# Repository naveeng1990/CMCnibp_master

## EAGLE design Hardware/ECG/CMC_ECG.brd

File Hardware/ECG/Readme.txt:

Contains ecg pre-amplifier board design

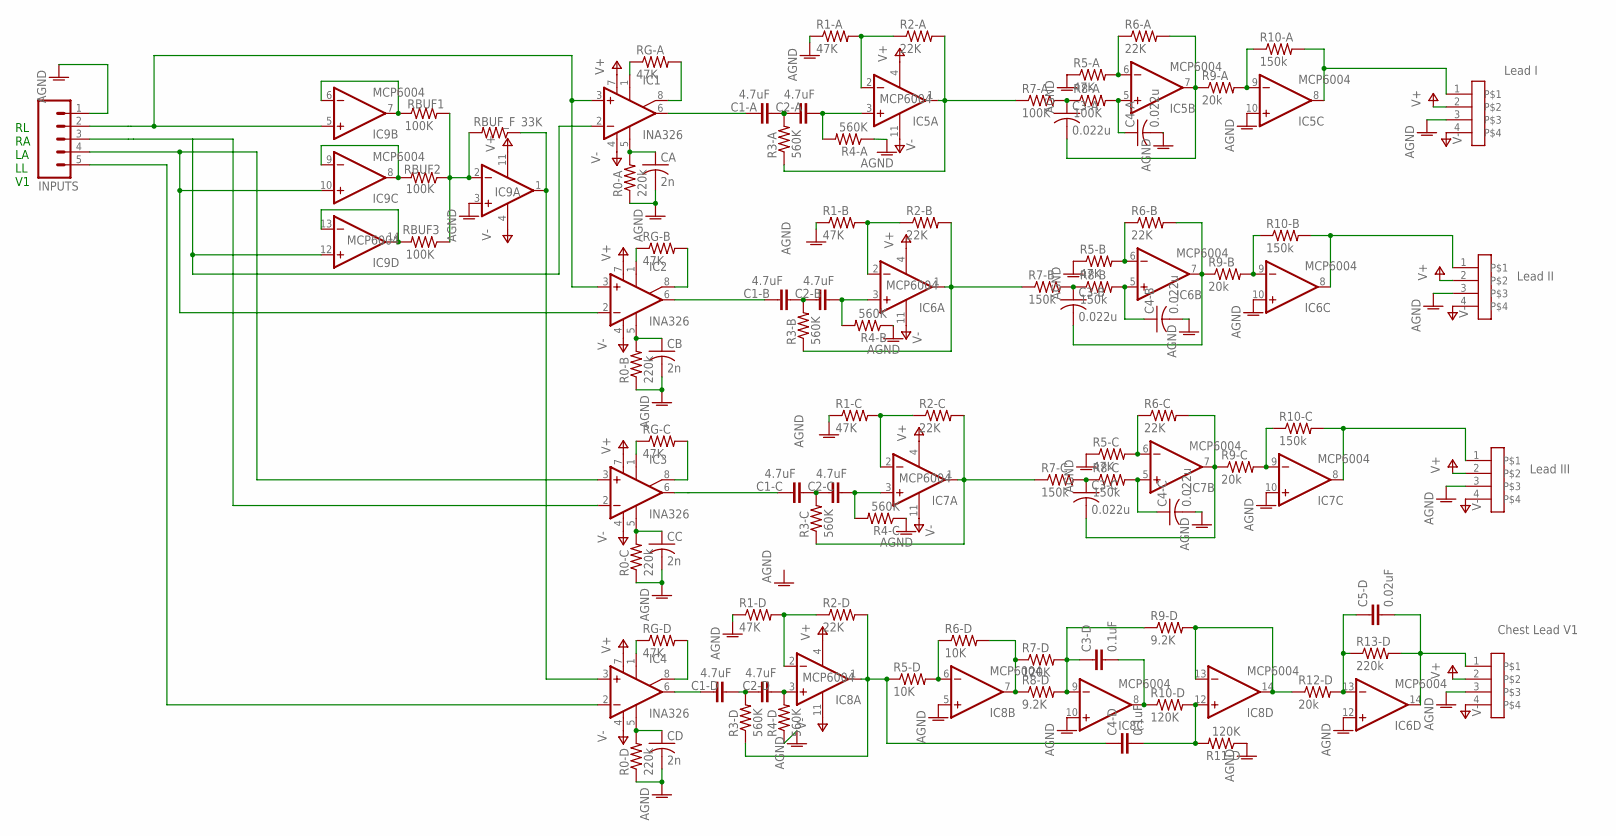
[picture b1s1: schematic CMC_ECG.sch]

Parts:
C1-A, C1-B, C1-C, C1-D, C2-A, C2-B, C2-C, C2-D: 4.7uF; C0805
C3-A, C3-B, C3-C, C4-A, C4-B, C4-C: 0.022u; C0805
C3-D, C4-D: 0.1uF; C0805
C5-D: 0.02uF; C0805
CA: 2n; C0805
CB: 2n; C0805
CC: 2n; C0805
CD: 2n; C0805
CHEST-V3: CON-4PIN_SIL; CON-4PIN-SIL
IC1, IC2, IC3, IC4: INA326; MSOP-08
IC5, IC6, IC7, IC8, IC9: MCP6004; TSSOP14
INPUTS: M05; 05P
LEAD-I: CON-4PIN_SIL; CON-4PIN-SIL
LEAD-II, LEAD-II1: CON-4PIN_SIL; CON-4PIN-SIL
R0-A, R0-B, R0-C, R0-D, R13-D: 220k; R0805
R1-A, R1-B, R1-C, R1-D, R5-A, R5-B, R5-C: 47K; R0805
R2-A, R2-B, R2-C, R2-D, R6-A, R6-B, R6-C: 22K; R0805
R3-A, R3-B, R3-C, R3-D, R4-A, R4-B, R4-C, R4-D: 560K; R0805
R5-D, R6-D: 10K; R0805
R7-A, R8-A: 100K; R0805
R7-B, R7-C, R8-B, R8-C, R10-A, R10-B, R10-C: 150k; R0805
R7-D, R10-D, R11-D: 120K; R0805
R8-D, R9-D: 9.2K; R0805
R9-A, R9-B, R9-C, R12-D: 20k; R0805
RBUF1, RBUF2, RBUF3: 100K; R0805
RBUF_F: 33K; R0805
RG-A: 47K; R0805
RG-B: 47K; R0805
RG-C: 47K; R0805
RG-D: 47K; R0805

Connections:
AGND: C4-A.2, C4-B.2, C4-C.2, CA.2, CB.2, CC.2, CD.2, CHEST-V3.3, IC5.10 (+IN), IC6.10 (+IN), IC6.12 (+IN), IC7.10 (+IN), IC8.5 (+IN), IC8.10 (+IN), IC9.3 (+IN), INPUTS.1, LEAD-I.3, LEAD-II.3, LEAD-II1.3, R0-A.1, R0-B.1, R0-C.1, R0-D.1, R1-A.1, R1-B.1, R1-C.1, R1-D.1, R4-A.1, R4-B.1, R4-C.1, R4-D.1, R5-A.1, R5-B.1, R5-C.1, R11-D.1
HPF-OUT: IC5.1 (OUT), R2-A.2, R3-A.1, R7-A.1
HPF-OUT1: IC6.1 (OUT), R2-B.2, R3-B.1, R7-B.1
HPF-OUT2: IC7.1 (OUT), R2-C.2, R3-C.1, R7-C.1
HPF-OUT3: C4-D.1, IC8.1 (OUT), R2-D.2, R3-D.1, R5-D.1
INA-OUT: C1-A.1, IC1.6 (OUT)
INA-OUT1: C1-B.1, IC2.6 (OUT)
INA-OUT2: C1-C.1, IC3.6 (OUT)
unnamed: IC1.8 (R1B), RG-A.2
unnamed: CA.1, IC1.5 (R2), R0-A.2
unnamed: C4-A.1, IC5.5 (+IN), R8-A.2
unnamed: IC1.1 (R1), RG-A.1
unnamed: C3-A.1, R7-A.2, R8-A.1
unnamed: C3-A.2, IC5.7 (OUT), R6-A.2, R9-A.1
unnamed: CD.1, IC4.5 (R2), R0-D.2
unnamed: CB.1, IC2.5 (R2), R0-B.2
unnamed: IC5.6 (-IN), R5-A.2, R6-A.1
unnamed: IC2.1 (R1), RG-B.1
unnamed: C1-A.2, C2-A.1, R3-A.2
unnamed: C2-A.2, IC5.3 (+IN), R4-A.2
unnamed: IC5.2 (-IN), R1-A.2, R2-A.1
unnamed: C1-B.2, C2-B.1, R3-B.2
unnamed: C2-B.2, IC6.3 (+IN), R4-B.2
unnamed: IC6.2 (-IN), R1-B.2, R2-B.1
unnamed: IC2.8 (R1B), RG-B.2
unnamed: C3-B.1, R7-B.2, R8-B.1
unnamed: C3-B.2, IC6.7 (OUT), R6-B.2, R9-B.1
unnamed: IC6.6 (-IN), R5-B.2, R6-B.1
unnamed: C4-B.1, IC6.5 (+IN), R8-B.2
unnamed: IC1.2 (-IN), IC3.2 (-IN), IC9.12 (+IN), INPUTS.3
unnamed: CC.1, IC3.5 (R2), R0-C.2
unnamed: IC3.1 (R1), RG-C.1
unnamed: C1-C.2, C2-C.1, R3-C.2
unnamed: C2-C.2, IC7.3 (+IN), R4-C.2
unnamed: IC7.2 (-IN), R1-C.2, R2-C.1
unnamed: IC3.8 (R1B), RG-C.2
unnamed: C3-C.1, R7-C.2, R8-C.1
unnamed: C3-C.2, IC7.7 (OUT), R6-C.2, R9-C.1
unnamed: IC7.6 (-IN), R5-C.2, R6-C.1
unnamed: C4-C.1, IC7.5 (+IN), R8-C.2
unnamed: IC4.2 (-IN), INPUTS.5
unnamed: IC7.9 (-IN), R9-C.2, R10-C.1
unnamed: C1-D.2, C2-D.1, R3-D.2
unnamed: IC7.8 (OUT), LEAD-II1.1, R10-C.2
unnamed: IC9.6 (-IN), IC9.7 (OUT), RBUF1.1
unnamed: IC9.8 (OUT), IC9.9 (-IN), RBUF2.2
unnamed: IC9.13 (-IN), IC9.14 (OUT), RBUF3.2
unnamed: IC9.2 (-IN), RBUF1.2, RBUF2.1, RBUF3.1, RBUF_F.2
unnamed: C2-D.2, IC8.3 (+IN), R4-D.2
unnamed: IC2.2 (-IN), IC3.3 (+IN), IC9.10 (+IN), INPUTS.4
unnamed: IC4.1 (R1), RG-D.1
unnamed: IC4.8 (R1B), RG-D.2
unnamed: IC8.2 (-IN), R1-D.2, R2-D.1
unnamed: IC8.6 (-IN), R5-D.2, R6-D.1
unnamed: C1-D.1, IC4.6 (OUT)
unnamed: IC8.7 (OUT), R6-D.2, R7-D.1, R8-D.1
unnamed: C3-D.1, IC8.9 (-IN), R7-D.2, R8-D.2, R9-D.1
unnamed: C3-D.2, IC8.8 (OUT), R10-D.1
unnamed: C4-D.2, IC8.12 (+IN), R10-D.2, R11-D.2
unnamed: IC8.13 (-IN), IC8.14 (OUT), R9-D.2, R12-D.1
unnamed: IC5.9 (-IN), R9-A.2, R10-A.1
unnamed: IC6.9 (-IN), R9-B.2, R10-B.1
unnamed: C5-D.1, IC6.13 (-IN), R12-D.2, R13-D.1
unnamed: C5-D.2, CHEST-V3.1, IC6.14 (OUT), R13-D.2
unnamed: IC6.8 (OUT), LEAD-II.1, R10-B.2
unnamed: IC5.8 (OUT), LEAD-I.1, R10-A.2
V+: CHEST-V3.2, IC1.7 (+VS), IC2.7 (+VS), IC3.7 (+VS), IC4.7 (+VS), IC5.4 (V+), IC6.4 (V+), IC7.4 (V+), IC8.4 (V+), IC9.11 (V-), LEAD-I.2, LEAD-II.2, LEAD-II1.2
V-: CHEST-V3.4, IC1.4 (-VS), IC2.4 (-VS), IC3.4 (-VS), IC4.4 (-VS), IC5.11 (V-), IC6.11 (V-), IC7.11 (V-), IC8.11 (V-), IC9.4 (V+), LEAD-I.4, LEAD-II.4, LEAD-II1.4
VIN+: IC1.3 (+IN), IC2.3 (+IN), IC9.5 (+IN), INPUTS.2
VIN+1: IC4.3 (+IN), IC9.1 (OUT), RBUF_F.1

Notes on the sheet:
Lead I
Lead II
Chest Lead V1
Lead III
RL RA LA LL V1

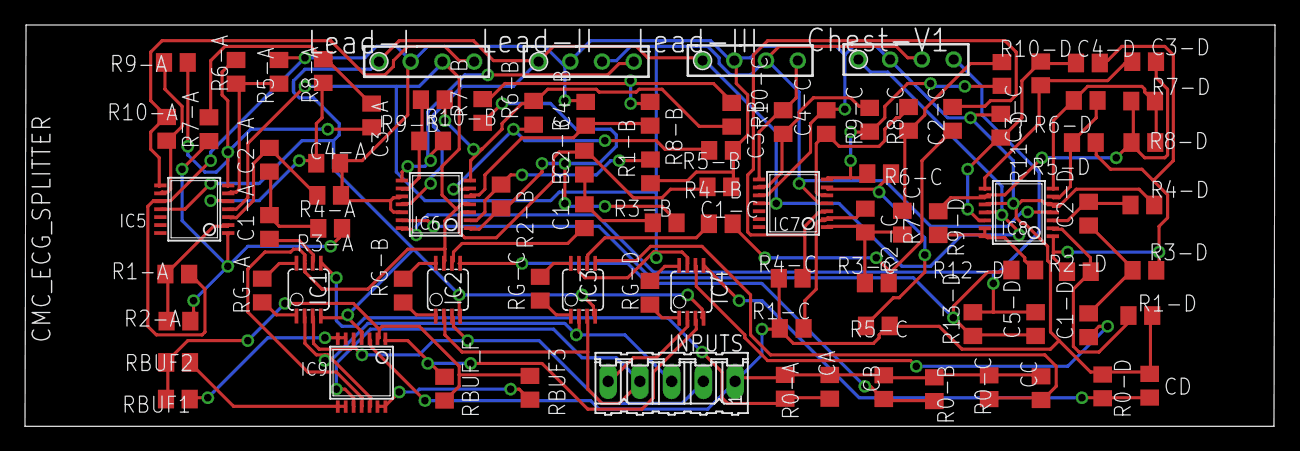
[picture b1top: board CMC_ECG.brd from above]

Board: 2 copper layers, 100.0 x 32.1 mm, 90 parts (0 on the bottom side), 70 nets.

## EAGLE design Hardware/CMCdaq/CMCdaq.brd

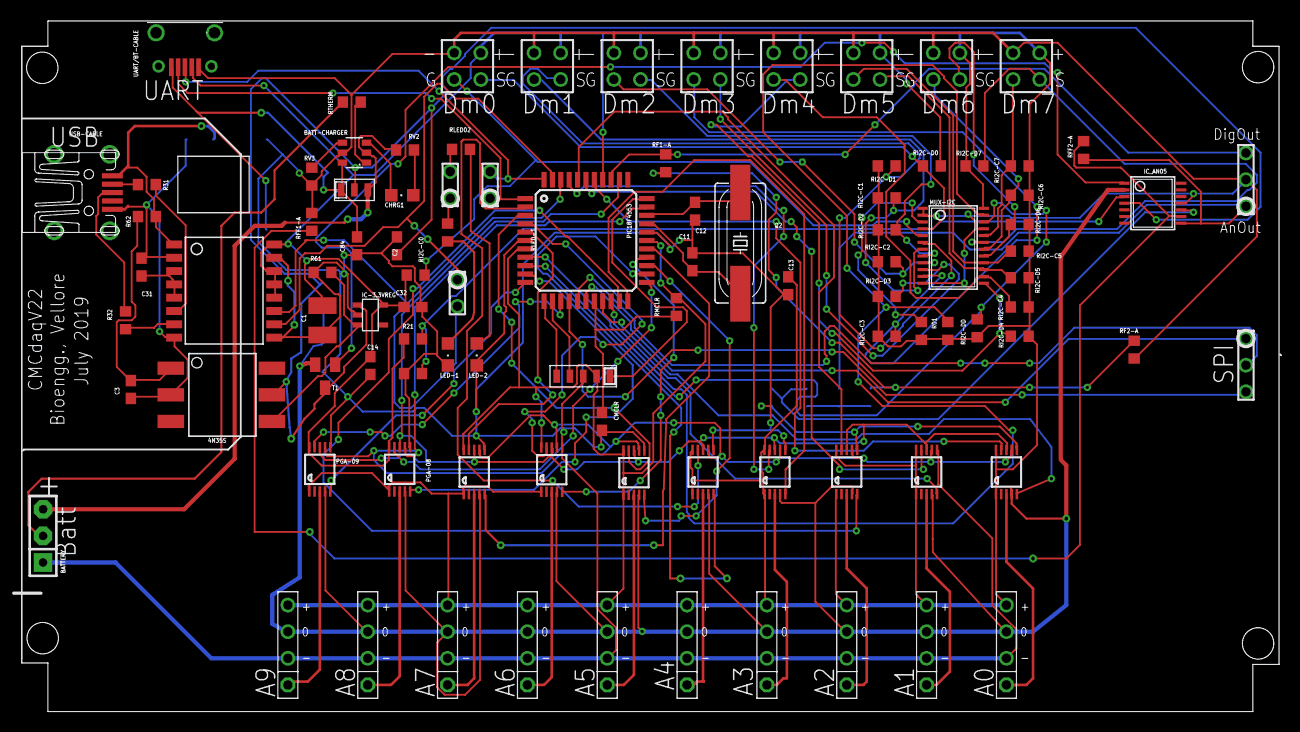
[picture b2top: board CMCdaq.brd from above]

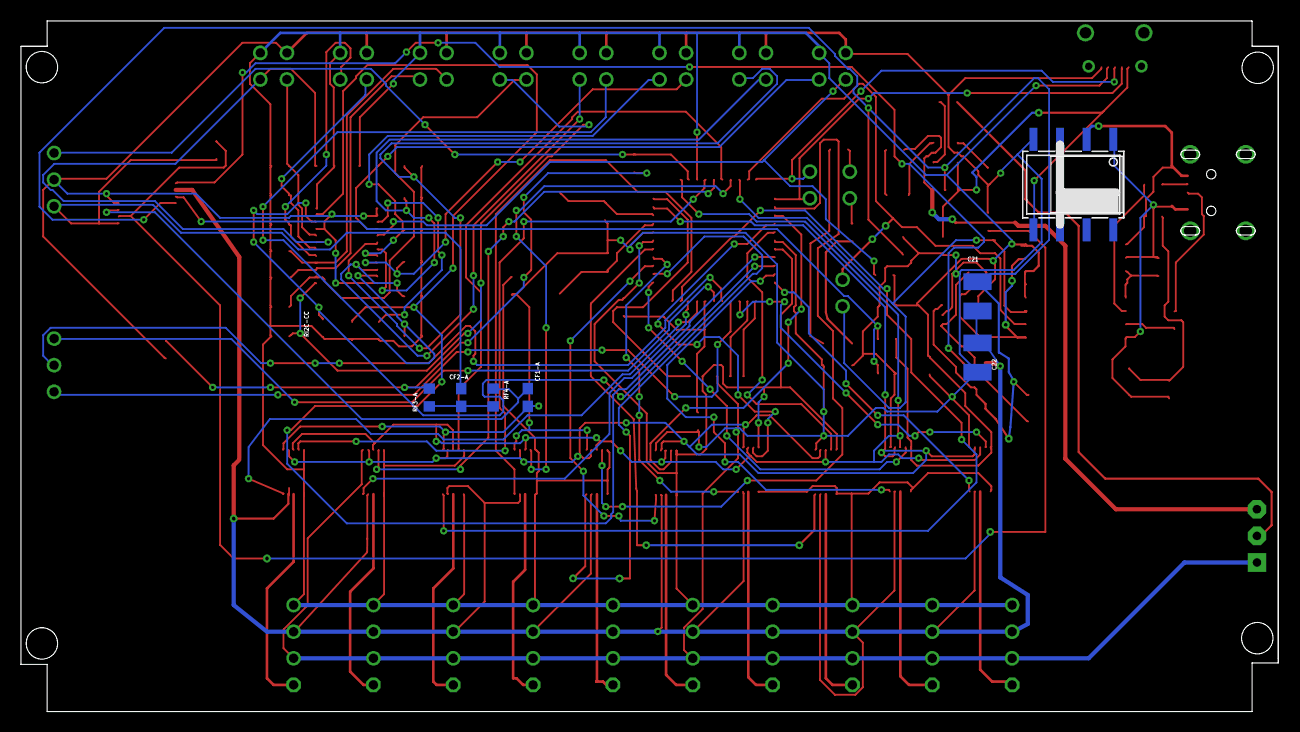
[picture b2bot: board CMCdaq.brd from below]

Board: 2 copper layers, 120.0 x 65.9 mm, 103 parts (7 on the bottom side), 96 nets.

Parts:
4N35S: 4N35S; SMD6
BATT-CHARGER: BG21040; SOT23-6
BATTERY: F-1X03-SIP-100-32; SIP-100-03-32
C1, C21, C22: 100uF; C1210
C2, C31, C32: 1uF; C0603
C3, C13, C14, C84: 0.1uF; C0603
C11, C12: 15pF; C0603
CF1-A, CF2-A: 0.1u; C0603
CHRG1: chrg; CHIPLED_0805
CMCLR: 0.1u; C0603
DAC/DOUT: CON-3PINDRILL; CON-3PIN
I2CMOD1, I2CMOD2, I2CMOD3, I2CMOD4, I2CMOD5, I2CMOD6, I2CMOD7, I2CMOD-0: CABLE-4PIN; CON-4PIN
IC30: ADUM4160; SOIC16-1
IC-3.3VREG: LDO-MIC5307; SOT23-5
ICSP: CON-5PINSMD; CON-5PIN-SMD
IC_AN05: MCP6004; TSSOP14
LED: CON-2PIN''STD"; CON-2PIN
LED-1, LED-2: B; CHIPLED_0805
MUX-I2C: TCA9548-I2CMUX; TSSOP24
PGA-00, PGA-01, PGA-02, PGA-03, PGA-04, PGA-05, PGA-06, PGA-07, PGA-08, PGA-09: PGA113; MSOP10
PIC18F4553: PIC18F4550_TQFP; TQFP44
PWR-USB/BATT: CON-3PINSMD; CON-3PIN-SMD
Q2: 20MHz; HC49UP
R01, R21, R22: 100K; R0603
R31, R32: 47E; R0603
R61: 1K; R0603
R62: 330E; R0603
RF1-A, RF2-A, RF3-A, RF4-A: 82K; R0603
RFF1-A: 7.8K; R0603
RFF2-A: 10K; R0603
RI2C-C0, RI2C-C1, RI2C-C2, RI2C-C3, RI2C-C4, RI2C-C5, RI2C-C6, RI2C-C7, RI2C-CC, RI2C-D0, RI2C-D1, RI2C-D2, RI2C-D3, RI2C-D4, RI2C-D5, RI2C-D6, RI2C-D7, RI2C-DD: 5K; R0603
RLED02: 330E; R0603
RLED-1: 330E; R0603
RMCLR: 10K; R0603
RTHERM: 1k; R0603
RV2, RV3: 1k; R0603
SPI: CON-3PINDRILL; CON-3PIN
T1: 2N3904; SOT23-BEC
U$1, U$2, U$3, U$4, U$5, U$6, U$7, U$8, U$9, U$10: CON-4PIN_SIL; CONN-4PINSIL2
UART: CON-2PIN''STD"; CON-2PIN
UART/BT-CABLE: UART; MICRO-USB1
USB-CABLE: USB-port; MINI-USB
USB-DATA: CON-2PIN''STD"; CON-2PIN
VBT-ISOLPWR: VBT1-SMT; SO08-GW

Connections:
+3V3: C1.1, C13.1, C14.1, C32.2, I2CMOD1.2, I2CMOD2.2, I2CMOD3.2, I2CMOD4.2, I2CMOD5.2, I2CMOD6.2, I2CMOD7.2, I2CMOD-0.2, IC30.12, IC30.13, IC30.14, IC30.16, IC-3.3VREG.5, ICSP.P$2, MUX-I2C.24, PGA-00.1, PGA-00.10, PGA-01.1, PGA-01.10, PGA-02.1, PGA-02.10, PGA-03.1, PGA-03.10, PGA-04.1, PGA-04.10, PGA-05.1, PGA-05.10, PGA-06.1, PGA-06.10, PGA-07.1, PGA-07.10, PGA-08.1, PGA-08.10, PGA-09.1, PGA-09.10, PIC18F4553.7, PIC18F4553.28, PIC18F4553.37, R01.1, R21.1, RI2C-C0.1, RI2C-C1.1, RI2C-C2.1, RI2C-C3.1, RI2C-C4.1, RI2C-C5.1, RI2C-C6.1, RI2C-C7.1, RI2C-CC.1, RI2C-D0.1, RI2C-D1.1, RI2C-D2.1, RI2C-D3.1, RI2C-D4.1, RI2C-D5.1, RI2C-D6.1, RI2C-D7.1, RI2C-DD.1, RMCLR.1, U$1.V+, U$2.V+, U$3.V+, U$4.V+, U$5.V+, U$6.V+, U$7.V+, U$8.V+, U$9.V+, U$10.V+, UART/BT-CABLE.2
+4.1V: BATT-CHARGER.2, BATTERY.3, PWR-USB/BATT.P$3, RV2.1
+5V: BATT-CHARGER.6, C84.1, PWR-USB/BATT.P$1, UART/BT-CABLE.5, VBT-ISOLPWR.5
+UB: 4N35S.P$5, C2.1, C21.1, IC-3.3VREG.1, IC_AN05.4, PWR-USB/BATT.P$2, T1.C
+VUSB: IC30.1, R62.1, USB-CABLE.1, VBT-ISOLPWR.2
-VUSB: 4N35S.P$2, C3.2, C31.1, IC30.2, IC30.8, USB-CABLE.5, VBT-ISOLPWR.1
AGND: C21.2, C22.1, IC_AN05.2, PGA-00.4, PGA-01.4, PGA-02.4, PGA-03.4, PGA-04.4, PGA-05.4, PGA-06.4, PGA-07.4, PGA-08.4, PGA-09.4, T1.E, U$1.AGND, U$2.AGND, U$3.AGND, U$4.AGND, U$5.AGND, U$6.AGND, U$7.AGND, U$8.AGND, U$9.AGND, U$10.AGND
AN0: PGA-00.5, PIC18F4553.19
AN1: PGA-01.5, PIC18F4553.20
AN2: PGA-02.5, PIC18F4553.21
AN3: PGA-03.5, PIC18F4553.22
AN4: PGA-04.5, PIC18F4553.24
AN5: PGA-05.5, PIC18F4553.25
AN6: PGA-06.5, PIC18F4553.26
AN7: PGA-07.5, PIC18F4553.27
AN8: PGA-08.5, PIC18F4553.10
AN9: PGA-09.5, PIC18F4553.11
BATT-TEMP: BATTERY.2, RTHERM.2
CABLE-TX/PIC-RX: PIC18F4553.1, UART.1, UART/BT-CABLE.4
CH-00: PGA-00.3, U$1.SIG
CH-01: PGA-01.3, U$2.SIG
CH-02: PGA-02.3, U$3.SIG
CH-03: PGA-03.3, U$4.SIG
CH-04: PGA-04.3, U$5.SIG
CH-05: PGA-05.3, U$6.SIG
CH-06: PGA-06.3, U$7.SIG
CH-07: PGA-07.3, U$8.SIG
CH-08: PGA-08.3, U$9.SIG
CH-09: PGA-09.3, U$10.SIG
DAC: CF2-A.1, DAC/DOUT.1, IC_AN05.8, RFF2-A.1
FILTA-0: RF1-A.2, RF2-A.1, RF3-A.2
FILTA-1: CF2-A.2, RF3-A.1, RF4-A.2
FILTA-2: CF1-A.1, IC_AN05.10, RF4-A.1
FILTA-3: IC_AN05.9, RFF1-A.1, RFF2-A.2
I2C_C-0: I2CMOD-0.3, MUX-I2C.5, RI2C-C0.2
I2C_C-1: I2CMOD1.3, MUX-I2C.7, RI2C-C1.2
I2C_C-2: I2CMOD2.3, MUX-I2C.9, RI2C-C2.2
I2C_C-3: I2CMOD3.3, MUX-I2C.11, RI2C-C3.2
I2C_C-4: I2CMOD4.3, MUX-I2C.14, RI2C-C4.2
I2C_C-5: I2CMOD5.3, MUX-I2C.16, RI2C-C5.2
I2C_C-6: I2CMOD6.3, MUX-I2C.18, RI2C-C6.2
I2C_C-7: I2CMOD7.3, MUX-I2C.20, RI2C-C7.2
I2C_D-0: I2CMOD-0.4, MUX-I2C.4, RI2C-D0.2
I2C_D-1: I2CMOD1.4, MUX-I2C.6, RI2C-D1.2
I2C_D-2: I2CMOD2.4, MUX-I2C.8, RI2C-D2.2
I2C_D-3: I2CMOD3.4, MUX-I2C.10, RI2C-D3.2
I2C_D-4: I2CMOD4.4, MUX-I2C.13, RI2C-D4.2
I2C_D-5: I2CMOD5.4, MUX-I2C.15, RI2C-D5.2
I2C_D-6: I2CMOD6.4, MUX-I2C.17, RI2C-D6.2
I2C_D-7: I2CMOD7.4, MUX-I2C.19, RI2C-D7.2
unnamed: R32.1, USB-CABLE.3
unnamed: MUX-I2C.23, PIC18F4553.8, RI2C-DD.2
unnamed: 4N35S.P$4, IC-3.3VREG.3, R61.1
unnamed: MUX-I2C.22, PIC18F4553.9, RI2C-CC.2
unnamed: LED-1.A, RLED-1.1
unnamed: LED-2.A, RLED02.1
unnamed: C31.2, IC30.3, IC30.4, IC30.5
unnamed: IC_AN05.1, T1.B
unnamed: BATT-CHARGER.4, RV3.2
unnamed: BATT-CHARGER.3, CHRG1.C
unnamed: IC_AN05.3, R21.2, R22.1
unnamed: CHRG1.A, RV2.2
unnamed: LED.1, RLED-1.2
unnamed: LED.2, RLED02.2
unnamed: 4N35S.P$1, C3.1, R62.2
unnamed: BATT-CHARGER.1, RTHERM.1
unnamed: C11.1, PIC18F4553.30, Q2.2
unnamed: CMCLR.1, PIC18F4553.18, RMCLR.2
unnamed: MUX-I2C.3, R01.2
N$D+: IC30.7, R32.2
N$D-: IC30.6, R31.2
N$D--: R31.1, USB-CABLE.2
OSC2: C12.1, PIC18F4553.31, Q2.1
PGA-CS00: PGA-00.9, PIC18F4553.38
PGA-CS01: PGA-01.9, PIC18F4553.39
PGA-CS02: PGA-02.9, PIC18F4553.40
PGA-CS03: PGA-03.9, PIC18F4553.41
PGA-CS04: PGA-04.9, PIC18F4553.2
PGA-CS05: PGA-05.9, PIC18F4553.3
PGA-CS06: PGA-06.9, PIC18F4553.4
PGA-CS07: PGA-07.9, PIC18F4553.5
PGA-CS08: PGA-08.9, PIC18F4553.23
PGA-CS09: PGA-09.9, PIC18F4553.14
PGA-SCK: PGA-00.7, PGA-01.7, PGA-02.7, PGA-03.7, PGA-04.7, PGA-05.7, PGA-06.7, PGA-07.7, PGA-08.7, PGA-09.7, PIC18F4553.32
PGA-SDA: PGA-00.8, PGA-01.8, PGA-02.8, PGA-03.8, PGA-04.8, PGA-05.8, PGA-06.8, PGA-07.8, PGA-08.8, PGA-09.8, PIC18F4553.35
PGC: ICSP.P$5, PIC18F4553.12
PGD: ICSP.P$4, PIC18F4553.13
PIC-TX/CABLE-RX: PIC18F4553.44, UART.2, UART/BT-CABLE.3
PWM-DIG: DAC/DOUT.3, PIC18F4553.36, RF1-A.1
SPI-SCK: PIC18F4553.17, SPI.1
SPI-SDI: PIC18F4553.15, SPI.3
SPI-SDO: PIC18F4553.16, SPI.2
USB-D+: IC30.10, PIC18F4553.43, USB-DATA.1
USB-D-: IC30.11, PIC18F4553.42, USB-DATA.2
VPP: ICSP.P$1, PIC18F4553.33
VSS: BATT-CHARGER.5, BATTERY.1, C1.2, C2.2, C11.2, C12.2, C13.2, C14.2, C22.2, C32.1, C84.2, CF1-A.2, CMCLR.2, DAC/DOUT.2, I2CMOD1.1, I2CMOD2.1, I2CMOD3.1, I2CMOD4.1, I2CMOD5.1, I2CMOD6.1, I2CMOD7.1, I2CMOD-0.1, IC30.9, IC30.15, IC-3.3VREG.2, ICSP.P$3, IC_AN05.11, LED-1.C, LED-2.C, MUX-I2C.1, MUX-I2C.2, MUX-I2C.12, MUX-I2C.21, PGA-00.6, PGA-01.6, PGA-02.6, PGA-03.6, PGA-04.6, PGA-05.6, PGA-06.6, PGA-07.6, PGA-08.6, PGA-09.6, PIC18F4553.6, PIC18F4553.29, R22.2, R61.2, RF2-A.2, RFF1-A.2, RV3.1, U$1.V-, U$2.V-, U$3.V-, U$4.V-, U$5.V-, U$6.V-, U$7.V-, U$8.V-, U$9.V-, U$10.V-, UART/BT-CABLE.1, VBT-ISOLPWR.4

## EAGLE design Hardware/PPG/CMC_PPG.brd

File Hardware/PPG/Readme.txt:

This version contains the schematic and layout for PPG board
The sensor is MAX30100, 3.3V supply

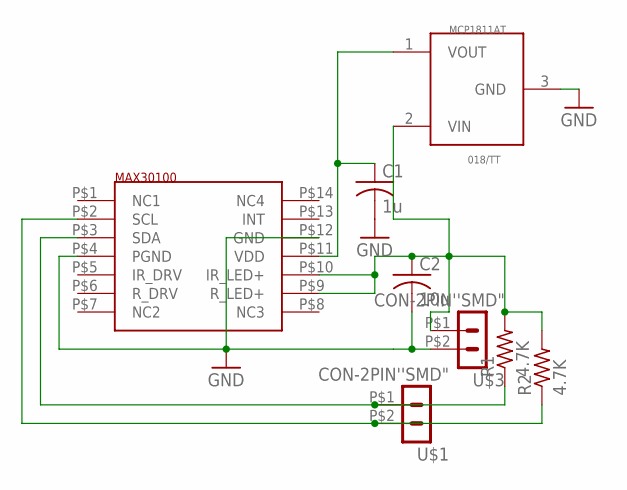
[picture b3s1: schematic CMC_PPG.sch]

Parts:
C1: 1u; C0805
C2: 10u; C0805
R1, R2: 4.7K; R0603
U$1, U$3: CON-2PIN''SMD"; CON-2PINSMD
U$2: OPTO_OXI_MAX30100
U$4: MCP1811AT-018/TTSMD; SOT23-3

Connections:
GND: C1.2, C2.2, U$2.P$4 (PGND), U$2.P$12 (GND), U$3.P$2 (2), U$4.3 (GND)
unnamed: C1.1, U$2.P$11 (VDD), U$4.1 (VOUT)
SCL: R2.1, U$1.P$2 (2), U$2.P$2 (SCL)
SDA: R1.1, U$1.P$1 (1), U$2.P$3 (SDA)
VDD: C2.1, R1.2, R2.2, U$2.P$9 (R_LED+), U$2.P$10 (IR_LED+), U$3.P$1 (1), U$4.2 (VIN)

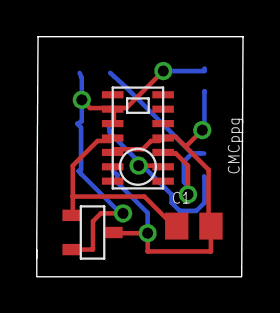
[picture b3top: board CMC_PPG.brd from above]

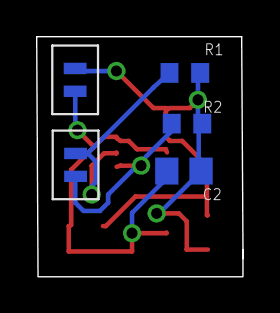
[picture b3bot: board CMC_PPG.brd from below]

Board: 2 copper layers, 11.5 x 13.3 mm, 8 parts (5 on the bottom side), 5 nets.

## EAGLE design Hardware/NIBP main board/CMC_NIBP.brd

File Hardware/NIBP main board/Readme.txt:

The NIBP main board is used to record data from 4 different sensors, such as
1. Cuff pressure
2. Intra-arterial pressure
3. 2 PPG signals

Hardware description
NIBP main board has
1. PIC microcontroller - start, stop, ramp up, transmits sensor signal to cmcdaq hardware
2. Two Pump(6V) and two valve to control cuff pressure
3. Self powered by Li--ION battery (3.6*2=7.4V) 
4. Battery charging circuit (Mobile phone charege micro-USB)
4. OLED display to show continuous cuff pressure
4. Start button(Green) to start the device and to do the ramp up operation
5. Stop button(rED) for emergency shutdown
6. CMCdaq software also controls the start and stop of data acquistion from sensors

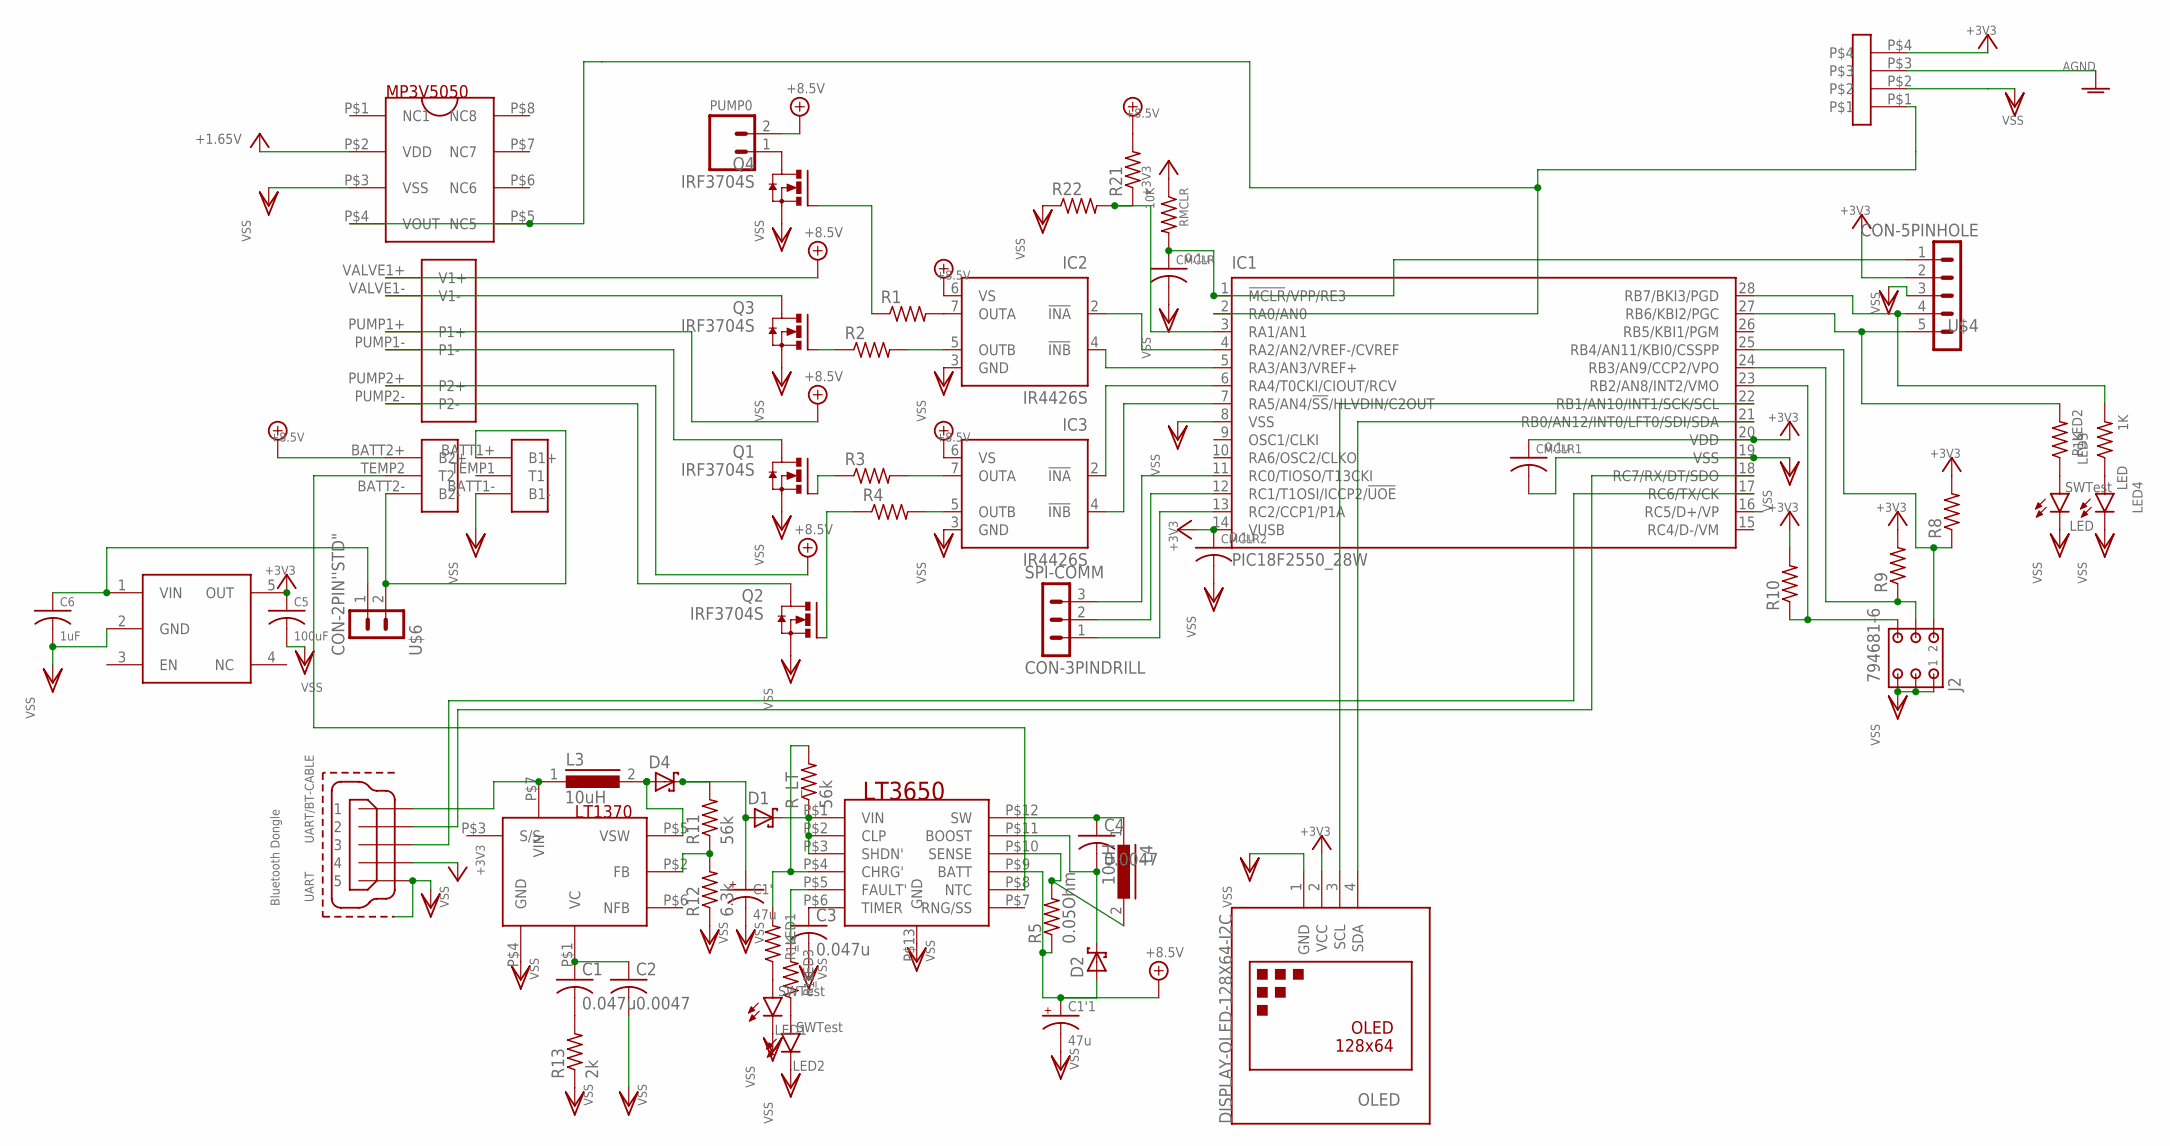
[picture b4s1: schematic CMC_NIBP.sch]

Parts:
C1, C3: 0.047u; C1206
C1', C1'1: 47u; E5-10,5
C2, C4: 0.0047; C1206
C5: 100uF; C1210
C6: 1uF; C0603
CMCLR, CMCLR1, CMCLR2: 0.1u; C0603
D1, D2, D4: SCHOTTKY-DIODESMD; SMB
IC1: PIC18F2550_28W; SO28W
IC2, IC3: IR4426S; SO08
IC-3.3VREG: LDO-MIC5307; SOT23-5
J2: 794681-6
L3, L4: 10uH; DR73
LED, LED1, LED2: SWTest; LED3MM
LED3: 1K; 0204V
LED4: LED; LED3MM
OLED: DISPLAY-OLED-128X64-I2C
PUMP0: Pump0; 02P
Q1, Q2, Q3, Q4: IRF3704S; D2PACK
R1, R2, R3, R4, R8, R9, R10, R21, R22: R-US_M1206; M1206
R5: 0.05Ohm; M1206
R11: 56k; M1206
R12: 6.3k; M1206
R13: 2k; M1206
RMCLR: 10K; R0603
R_LED1, R_LED2, R_LED3: 1K; 0204V
R_LT: 56k; M1206
SPI-COMM: CON-3PINDRILL; CON-3PIN
U$1: NIBP_PNEUMATICS; NIBP_PNEUM
U$2: LT1370; DD-PACK-7LEAD
U$3: LT3650; MSOP-12
U$4: CON-5PINHOLE; CON-5PIN
U$5: CON-4PIN_SIL; CONN-4PINSIL2
U$6: CON-2PIN''STD"; CON-2PIN
UART/BT-CABLE: UART; MICRO-USB1

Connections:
+3V3: C5.1, CMCLR1.1, CMCLR2.1, IC1.14 (VUSB), IC1.20 (VDD), IC-3.3VREG.5 (OUT), OLED.2 (VCC), R8.2, R9.2, R10.2, RMCLR.1, U$1.P$2 (VDD), U$4.2, U$5.P$4, UART/BT-CABLE.4
+9V: C1'1.+, D2.A, IC2.6 (VS), IC3.6 (VS), PUMP0.2, R5.1, R21.2, U$1.BATT2+ (B2+), U$1.PUMP1+ (P1+), U$1.PUMP2+ (P2+), U$1.VALVE1+ (V1+), U$3.P$9 (BATT)
+9V2: R_LED1.2, R_LT.2, U$3.P$4 (CHRG')
AGND: U$5.P$3
BATT-MONITOR: IC1.3 (RA1/AN1), R21.1, R22.2
DISP-SCL: IC1.22 (RB1/AN10/INT1/SCK/SCL), OLED.3 (SCL)
DISP-SDA: IC1.21 (RB0/AN12/INT0/LFT0/SDI/SDA), OLED.4 (SDA)
unnamed: PUMP0.1, Q4.2 (D)
unnamed: U$1.TEMP2 (T2), U$3.P$8 (NTC)
unnamed: R_LED3.2, U$3.P$5 (FAULT')
unnamed: LED2.A, R_LED3.1
unnamed: U$1.BATT1+ (B1+), U$1.BATT2- (B2-), U$6.2
unnamed: C6.1, IC-3.3VREG.1 (VIN), U$6.1
unnamed: Q2.1 (G), R4.1
unnamed: Q1.1 (G), R3.1
unnamed: Q4.1 (G), R1.1
unnamed: IC3.7 (OUTA), R3.2
unnamed: IC2.7 (OUTA), R1.2
unnamed: IC2.5 (OUTB), R2.2
unnamed: L3.1, U$2.P$7 (VIN), UART/BT-CABLE.1
unnamed: IC3.5 (OUTB), R4.2
unnamed: D4.A, L3.2, U$2.P$5 (VSW)
unnamed: LED3.1, LED4.A
unnamed: C1'.+, D1.A, D4.C, R11.2
unnamed: R11.1, R12.2, U$2.P$2 (FB)
unnamed: D1.C, R_LT.1, U$3.P$1 (VIN), U$3.P$2 (CLP), U$3.P$3 (SHDN')
unnamed: C1.1, C2.1, U$2.P$1 (VC)
unnamed: C1.2, R13.2
unnamed: C4.1, L4.1, U$3.P$12 (SW)
unnamed: C3.1, U$3.P$6 (TIMER)
unnamed: L4.2, R5.2, U$3.P$10 (SENSE)
unnamed: C4.2, D2.C, U$3.P$11 (BOOST)
unnamed: LED1.A, R_LED1.1
unnamed: LED.A, R_LED2.1
PGC: IC1.27 (RB6/KBI2/PGC), R_LED2.2, U$4.5
PGD: IC1.28 (RB7/BKI3/PGD), LED3.2, U$4.4
PIC-RX_CABLE-TX: IC1.18 (RC7/RX/DT/SDO), UART/BT-CABLE.2
PIC-TX_CABLE-RX: IC1.17 (RC6/TX/CK), UART/BT-CABLE.3
PRESSURE-SIG: IC1.2 (RA0/AN0), U$1.P$4 (VOUT), U$1.P$5 (NC5), U$5.P$1
PUMP1: Q1.2 (D), U$1.PUMP1- (P1-)
PUMP1-A: IC1.6 (RA4/T0CKI/CIOUT/RCV), IC3.2 (!INA)
PUMP2: Q2.2 (D), U$1.PUMP2- (P2-)
PUMP2-A: IC1.7 (RA5/AN4/!SS!/HLVDIN/C2OUT), IC3.4 (!INB)
SCK: IC1.11 (RC0/TIOSO/T13CKI), SPI-COMM.3
SDI: IC1.13 (RC2/CCP1/P1A), SPI-COMM.1
SDO: IC1.12 (RC1/T1OSI/ICCP2/!UOE), SPI-COMM.2
SW1: IC1.23 (RB2/AN8/INT2/VMO), J2.6, R10.1
SW2: IC1.24 (RB3/AN9/CCP2/VPO), J2.4, R9.1
SW3: IC1.25 (RB4/AN11/KBI0/CSSPP), J2.2, R8.1
VALVE1-A: IC1.4 (RA2/AN2/VREF-/CVREF), IC2.2 (!INA)
VALVE2: Q3.2 (D), U$1.VALVE1- (V1-)
VALVE2-A: IC1.5 (RA3/AN3/VREF+), IC2.4 (!INB)
VALVE2-B: Q3.1 (G), R2.1
VPP: CMCLR.1, IC1.1 (!MCLR!/VPP/RE3), RMCLR.2, U$4.1
VSS: C1'.-, C1'1.-, C2.2, C3.2, C5.2, C6.2, CMCLR.2, CMCLR1.2, CMCLR2.2, IC1.8 (VSS), IC1.19 (VSS), IC2.3 (GND), IC3.3 (GND), IC-3.3VREG.2 (GND), J2.1, J2.3, J2.5, LED.K (C), LED1.K (C), LED2.K (C), LED4.K (C), OLED.1 (GND), Q1.3 (S), Q2.3 (S), Q3.3 (S), Q4.3 (S), R12.1, R13.1, R22.1, U$1.BATT1- (B1-), U$1.P$3 (VSS), U$2.P$4 (GND), U$3.P$13 (GND), U$4.3, U$5.P$2, UART/BT-CABLE.5

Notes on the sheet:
Bluetooth Dongle

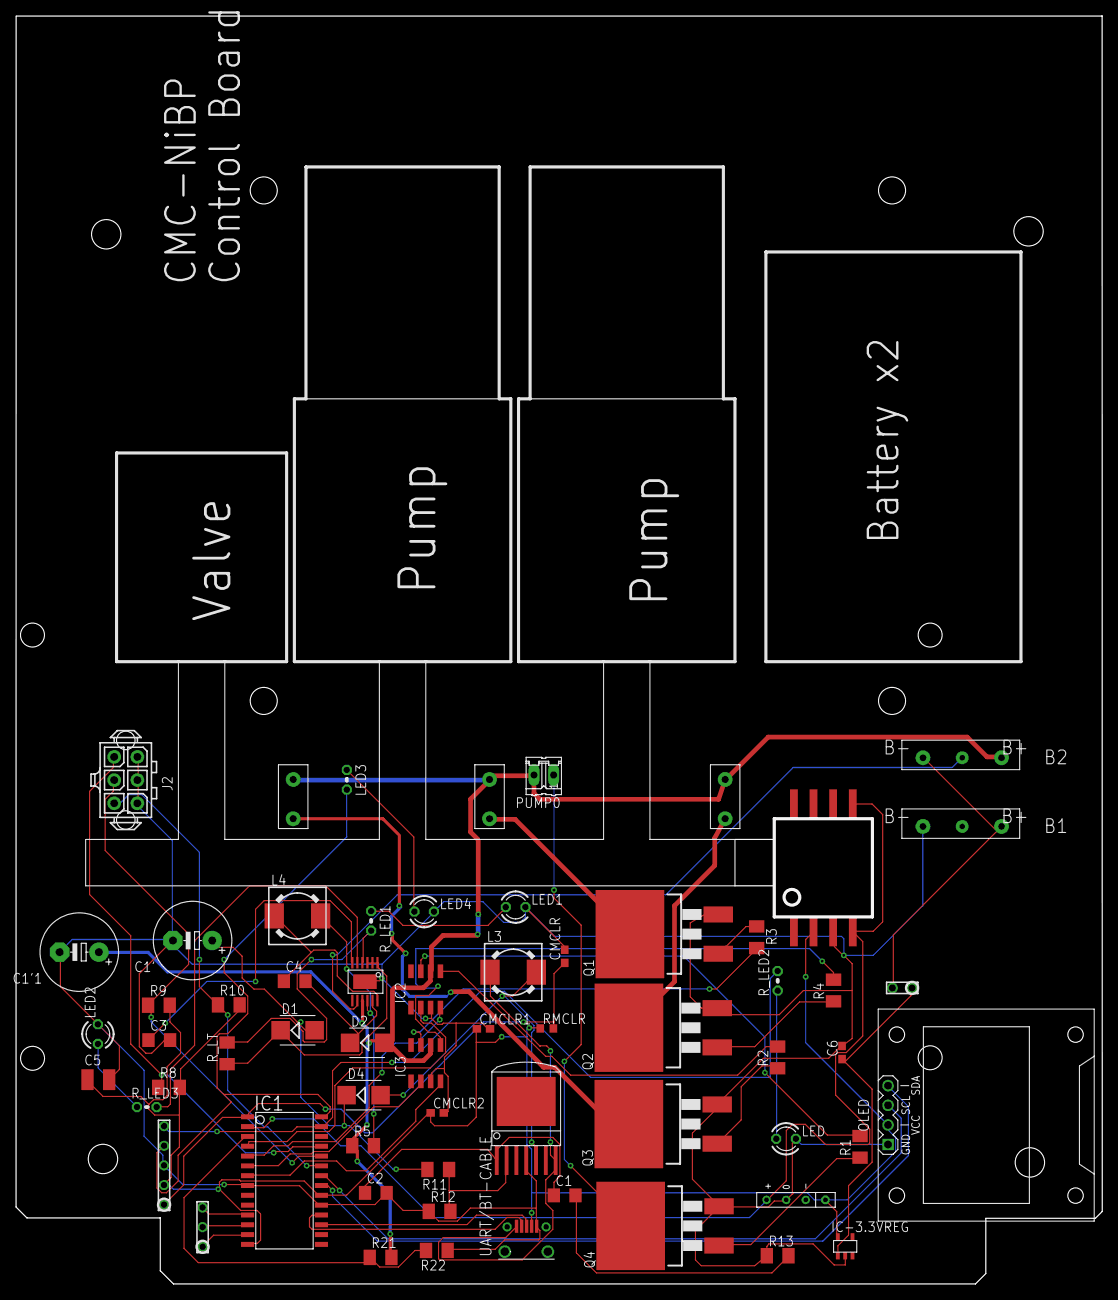
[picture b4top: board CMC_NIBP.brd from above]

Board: 2 copper layers, 140.5 x 164.0 mm, 58 parts (0 on the bottom side), 54 nets.

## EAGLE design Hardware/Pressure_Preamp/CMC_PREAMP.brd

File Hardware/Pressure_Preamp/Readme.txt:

COntains Board and schematic for version 0 Preamp - Pressure

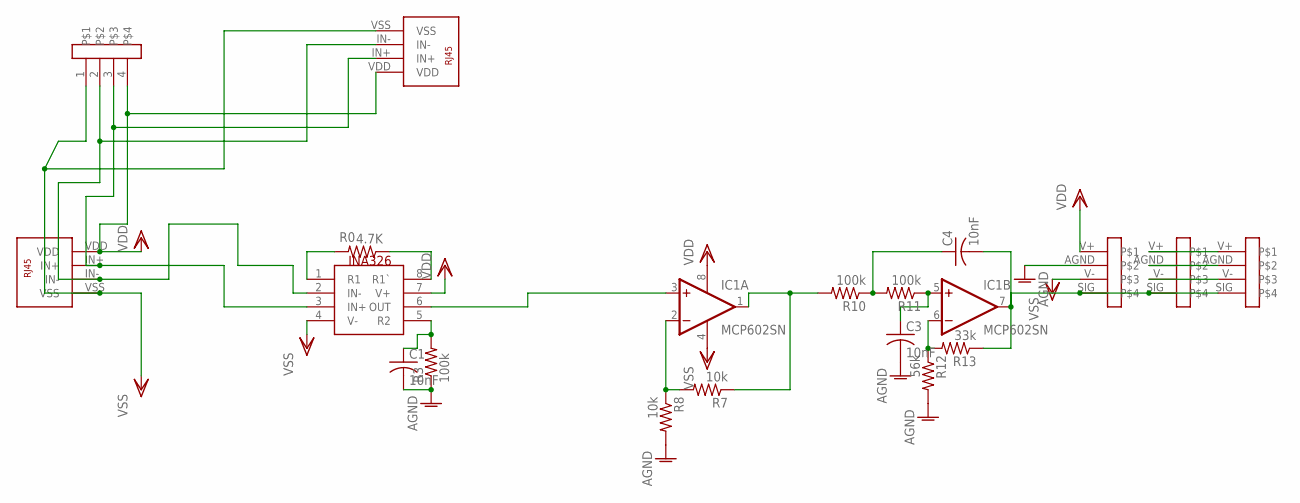
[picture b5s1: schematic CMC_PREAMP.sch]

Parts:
C1, C3, C4: 10nF; C0603
IC1: MCP602SN; SO08
R0: 4.7K; R0603
R3, R10, R11: 100k; R0603
R7, R8: 10k; R0603
R12: 56k; R0603
R13: 33k; R0603
U$1: CON-4PIN_SILHOLE; CON-4PIN-SIL
U$2, U$3, U$7: CON-4PIN_SIL; CONN-4PINSIL2
U$4, U$6: RJ45-PRESSUREHOLE; RJ45
U$8: INA326; MSOP08

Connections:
AGND: C1.2, C3.2, R3.1, R8.2, R12.2, U$7.AGND
AMP2-OUT: IC1.1 (OUT), R7.1, R10.2
AMP-IN+: U$1.3, U$4.IN+, U$6.IN+, U$8.3 (IN+)
AMP-IN-: U$1.2, U$4.IN-, U$6.IN-, U$8.2 (IN-)
INA-OUT1: IC1.3 (+IN), U$8.6 (OUT)
LPF-OUT: C4.2, IC1.7 (OUT), R13.1, U$2.SIG, U$3.SIG, U$7.SIG
unnamed: R0.2, U$8.1 (R1)
unnamed: U$2.V+, U$3.V+
unnamed: R0.1, U$8.8 (R1`)
unnamed: U$2.AGND, U$3.AGND
unnamed: U$2.V-, U$3.V-
unnamed: IC1.2 (-IN), R7.2, R8.1
unnamed: C4.1, R10.1, R11.2
unnamed: C1.1, R3.2, U$8.5 (R2)
unnamed: IC1.6 (-IN), R12.1, R13.2
unnamed: C3.1, IC1.5 (+IN), R11.1
VDD: IC1.8 (V+), U$1.4, U$4.VDD, U$6.VDD, U$7.V+, U$8.7 (V+)
VSS: IC1.4 (V-), U$1.1, U$4.VSS, U$6.VSS, U$7.V-, U$8.4 (V-)

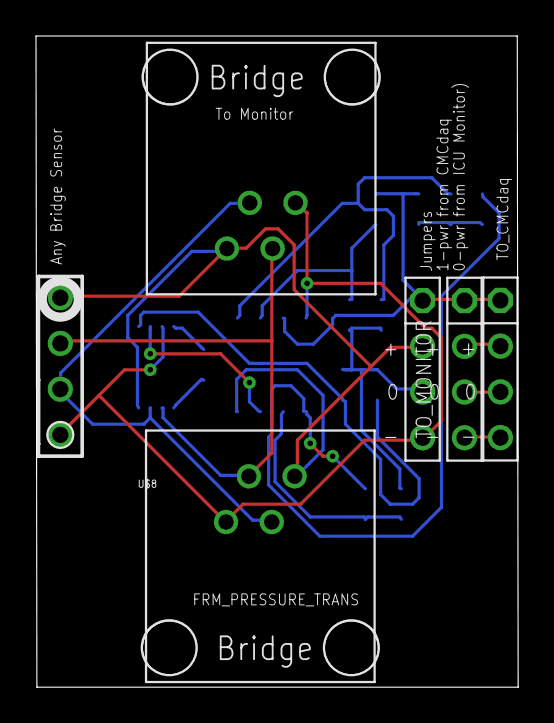
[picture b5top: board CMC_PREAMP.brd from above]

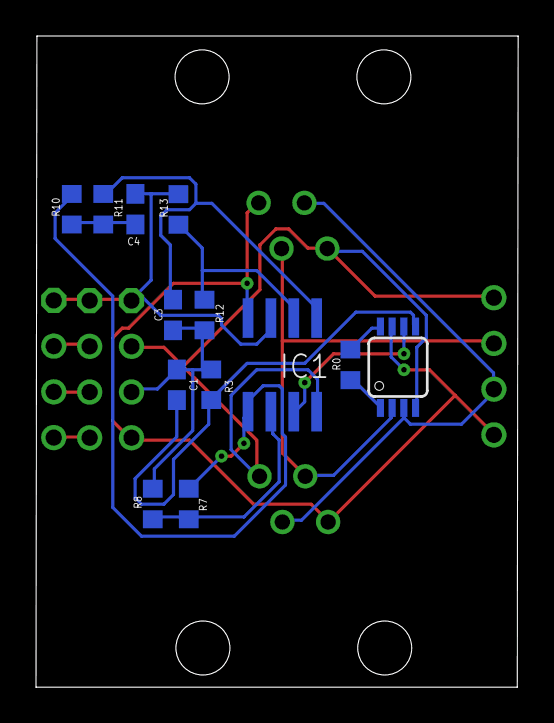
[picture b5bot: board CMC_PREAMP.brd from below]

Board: 2 copper layers, 26.8 x 36.2 mm, 19 parts (13 on the bottom side), 18 nets.

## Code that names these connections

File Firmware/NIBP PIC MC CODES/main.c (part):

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#include "ADC.h"
#include "SPI.h"

#define SWA         PORTBbits.RB0
#define SWB         PORTBbits.RB1
#define SWC         PORTBbits.RB2
#define LED1        PORTBbits.RB6
#define LED2        PORTBbits.RB7
#define VALVE1      PORTCbits.RC0
#define VALVE2      PORTCbits.RC1
#define PUMP1       PORTCbits.RC2
//#define PUMP2       PORTCbits.RC3
#define PUMP2       PORTBbits.RB3
#define LEVEL_DEF   0
#define LEVEL_LOAD  1

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    LATC = 0x00;
//    TRISB = 0x0F;
    TRISB = 0x07;
//    PORTBbits.RB3=0;
    TRISC = 0x00;
    
    
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    SSD1306_Begin(SSD1306_SWITCHCAPVCC);
    ADC_Init();
    SPI1_Init();
    PUMP1 = 0;
    PUMP2 = 0;
    VALVE1 = 1;
    VALVE2 = 1;
    
    lastBattery = ADC_BatteryLevel();
    if(lastBattery == 0) { errorBatt(); }
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    {
        UI_SetPress(pressureLevel[order]);
        VALVE1 = 0;
        VALVE2 = 0;
        PUMP1 = 1;
        PUMP2 = 1;
        pressureVal = ADC_ReadmmHg();
        while(pressureVal < pressureLevel[order]-GAP_SMOOTH)
        {   
            PUMP1 = 1;
            PUMP2 = 1;
            pressureVal = ADC_ReadmmHg();
            if(pressureVal >= pressureLevel[order]-GAP_SMOOTH) break;
            m_font = FONT_SIZE_MEDIUM;
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            if(pressureVal >= pressureLevel[order]-GAP_SMOOTH) break;
            if(SWB == 0) {VALVE1 = 1;VALVE2 = 1;PUMP1 = 0;PUMP2 = 0;return;}
        }
        PUMP1 = 0;
        PUMP2 = 0;  
        UI_ReadPress(pressureVal);
        for(i=0;i<65;i++) 
        {
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            else {PUMP1=0;PUMP2=0;}
            __delay_ms(10);
        }
        PUMP1 = 0;
        PUMP2 = 0;
        VALVE1 = 1;
        VALVE2 = 1;
        pressureVal = ADC_ReadmmHg();
        while(pressureVal > 0) //changed from 100
        {
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    
    UI_SetPress(190);
    VALVE1 = 0;
    VALVE2 = 0;
    PUMP1 = 1;
    pressureVal = ADC_ReadmmHg();
    while(pressureVal < 190)
    {
        __delay_ms(1);
        PUMP1 = 1;
        __delay_ms(15);
        PUMP1 = 0;
        pressureVal = ADC_ReadmmHg();
        UI_ReadPress(pressureVal);
        if(SWB == 0) {VALVE1 = 1;VALVE2 = 1;PUMP1 = 0;PUMP2 = 0;return;}
    }
    UI_ReadPress(pressureVal);
    PUMP1 = 0;
    VALVE1 = 1;
    VALVE2 = 1;
    while(pressureVal > 0)
    {
        pressureVal = ADC_ReadmmHg();
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
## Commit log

2021-05-01 nibp updates
2021-05-01 IEEE conf Latex file
2021-08-09 RC calculation for patient
    RC calculation for patient
2022-06-29 CMC NIBP analysis for sys and dia (Naveen's)
    All the CMC NIBP python codes (Naveen's) is uploaded.
    Versions after 2021 November.
2022-06-29 CMCnibp firmware(author-NaveenG)
    CMCnibp firmware(author-NaveenG) -pic18f27j13 embedded code
2022-06-29 Pulkesh patient R C analysis (author-NaveenG)

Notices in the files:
parts and their libraries:
con-headers-jp: Copyright (C) 2008, Bob Starr
diy-modules: Released under the Creative Commons Attribution 4.0 International License: http://creativecommons.org/licenses/by/4.0
